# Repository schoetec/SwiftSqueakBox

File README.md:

# SwiftSqueakBox

Een klein toestel (7cmx7cm) om het geluid van Gierzwaluwen te produceren met als doel zwaluwen naar nest-plaatsen te lokken.

**Waarschijnlijk ben je hier geraakt door de gierzwaluwcontactdag.** 

De Gierzwaluwwerkgroep vlaanderen :
https://www.natuurpunt.be/afdelingen/gierzwaluwenwerkgroep-vlaanderen

Email voor opmerkingen,vragen, bestellingen van printplaatjes of afgewerkte SSB's (enkel versie 3): swiftsqueakbox@gmail.com

**Belangrijk : de hier beschreven schakeling is enkel getest met de MP3 module, DFPlayer van DFRobot (https://www.dfrobot.com/product-1121.html). Wees voorzichtig met bv de MP3-TF-16P, deze ziet er gelijkaardig uit, maar is niet hetzelfde !! (En deze worden soms aangeboden onder de naam van DFPlayer !! ).
De software versie V5.1 werkt ook met MP3-TF-16P (myPlayer_attiny85_v5.1). Onderzoek naar een alternatief zonder deze module is gestart. Meer hierover later.**  

**Voor handleiding en ontwerp beschrijving zie de [project Wiki](https://github.com/schoetec/SwiftSqueakBox/wiki).**
 
**Het project is volledig open source/open hardware en de toegankelijkheid maakt dit een mooi STEM project**

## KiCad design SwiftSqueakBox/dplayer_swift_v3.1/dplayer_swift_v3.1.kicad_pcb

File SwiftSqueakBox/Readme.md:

# Structuur beschrijving

1. Arduino_Swift : bevat de software voor ATTiny84 en ATTiny85/45
2. dplayer_swift_v3.1 : Bevat de kicad 6.0 schema en PCB ontwerp files
3. KiCad_Arduino_Nano_DFPlayer_footprints-master : Bevat het ontwerp voor de DFPlayer kicad footprint.

# Bron verwijzingen:

## Arduino libraries voor dfplayer 
### DFPlayer - A Mini MP3 Player For Arduino

> DFPlayer - A Mini MP3 Player For Arduino
> https://www.dfrobot.com/index.php?route=product/product&product_id=1121
>
> This example shows the all the function of library for DFPlayer.
>
> Created 2016-12-07
> By [Angelo qiao](Angelo.qiao@dfrobot.com)
> 
> GNU Lesser General Public License.
> See <http://www.gnu.org/licenses/> for details.
> All above must be included in any redistribution
> 
> Notice and Trouble shooting
> 
> 1.Connection and Diagram can be found here
> https://www.dfrobot.com/wiki/index.php/DFPlayer_Mini_SKU:DFR0299#Connection_Diagram
> 2.This code is tested on Arduino Uno, Leonardo, Mega boards.

## Kicad footprint design. (deze heb je nodig voor de kicad PCB, dus eerst deze footprint opladen in de kicad footprint library)
### KiCad_Arduino_Nano_DFPlayer_footprints
> Footprints for Arduino Nano and DFPlayer MP3 player because I had to make them. 
>
> (I actually use a 32 pin socket to hold the nano to the board. eBay: 32 pin dip IC socket. 2x16.)
>
> There are already components out there for both, but I couldnt find a footprint.
>
> How
> * Add to your library directory.
> * Example: C:\Program Files\KiCad\share\kicad\library
> * Add library to Cvpcb app. Preferences->footprint libraries-> append with wizard

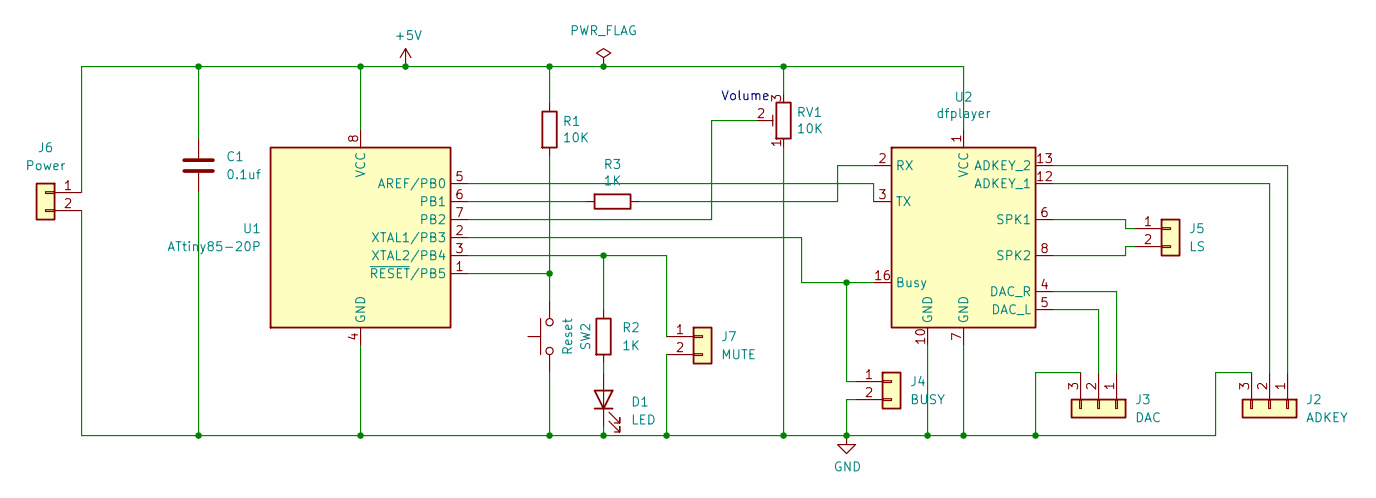
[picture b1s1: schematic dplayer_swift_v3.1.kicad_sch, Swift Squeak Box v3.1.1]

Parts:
C1: 0.1uf; C_Rect_L4.6mm_W2.0mm_P2.50mm_MKS02_FKP02
D1: LED; LED_D3.0mm
J2: ADKEY; JST_PH_B3B-PH-K_1x03_P2.00mm_Vertical
J3: DAC; JST_PH_B3B-PH-K_1x03_P2.00mm_Vertical
J4: BUSY; JST_PH_B2B-PH-K_1x02_P2.00mm_Vertical
J5: LS; JST_PH_B2B-PH-K_1x02_P2.00mm_Vertical
J6: Power; JST_PH_B2B-PH-K_1x02_P2.00mm_Vertical
J7: MUTE; JST_PH_B2B-PH-K_1x02_P2.00mm_Vertical
R1: 10K; R_Axial_DIN0207_L6.3mm_D2.5mm_P7.62mm_Horizontal
R2, R3: 1K; R_Axial_DIN0207_L6.3mm_D2.5mm_P7.62mm_Horizontal
RV1: 10K; Potentiometer_Piher_PT-10-V10_Vertical
SW2: Reset; SW_PUSH_6mm_H4.3mm
U1: ATtiny85-20P; DIP-8_W7.62mm
U2: dfplayer; DFPlayer

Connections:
+5V: C1.1, J6.1, R1.1, RV1.3, U1.8 (VCC), U2.1 (VCC)
GND: C1.2, D1.1 (K), J2.3, J3.3, J4.2, J6.2, J7.2, RV1.1, SW2.1, U1.4 (GND), U2.7 (GND), U2.10 (GND)
unnamed: D1.2 (A), R2.2
unnamed: J2.1, U2.13 (ADKEY_2)
unnamed: J2.2, U2.12 (ADKEY_1)
unnamed: J3.1, U2.4 (DAC_R)
unnamed: J3.2, U2.5 (DAC_L)
unnamed: J4.1, U1.2 (XTAL1/PB3), U2.16 (Busy)
unnamed: J5.1, U2.6 (SPK1)
unnamed: J5.2, U2.8 (SPK2)
unnamed: R1.2, SW2.2, U1.1 (~RESET/PB5)
unnamed: J7.1, R2.1, U1.3 (XTAL2/PB4)
unnamed: R3.1, U2.2 (RX)
unnamed: R3.2, U1.6 (PB1)
unnamed: RV1.2, U1.7 (PB2)
unnamed: U1.5 (AREF/PB0), U2.3 (TX)

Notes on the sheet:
Volume

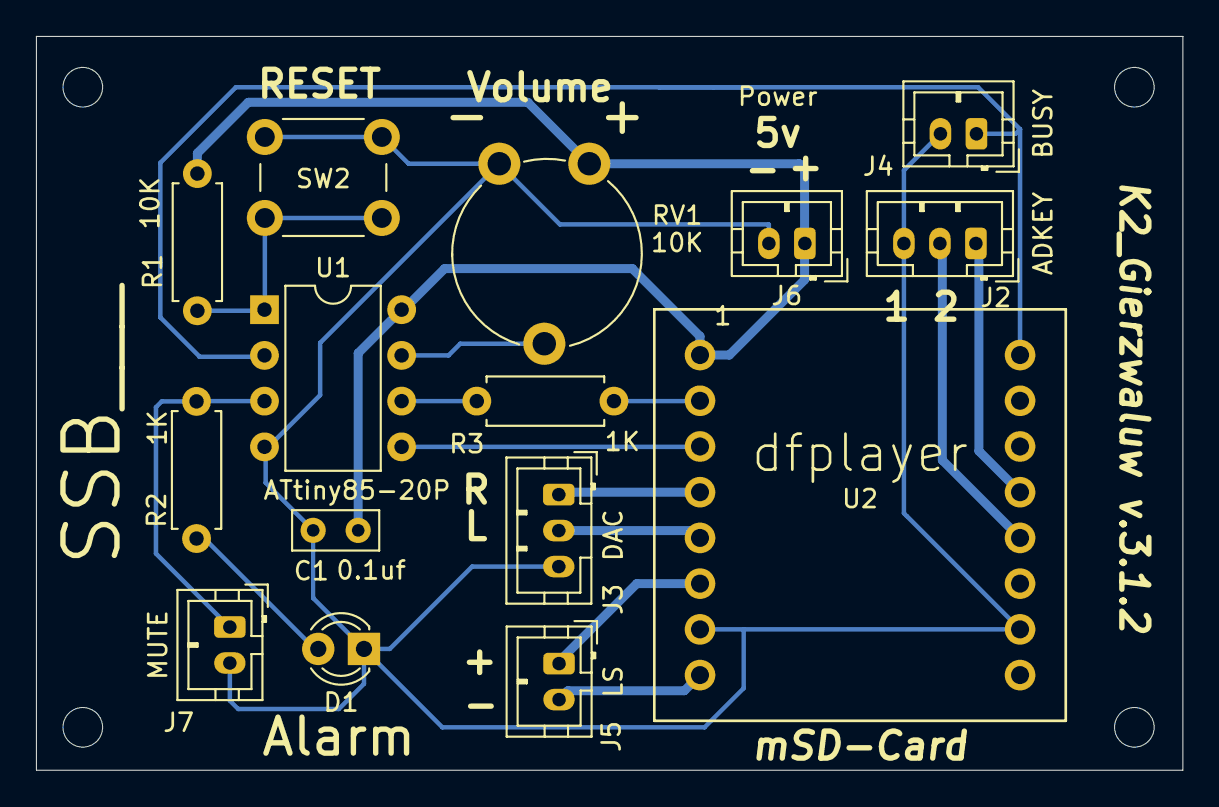
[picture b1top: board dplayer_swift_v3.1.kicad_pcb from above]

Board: 2 copper layers, 63.7 x 40.8 mm, 15 parts (0 on the bottom side), 16 nets.

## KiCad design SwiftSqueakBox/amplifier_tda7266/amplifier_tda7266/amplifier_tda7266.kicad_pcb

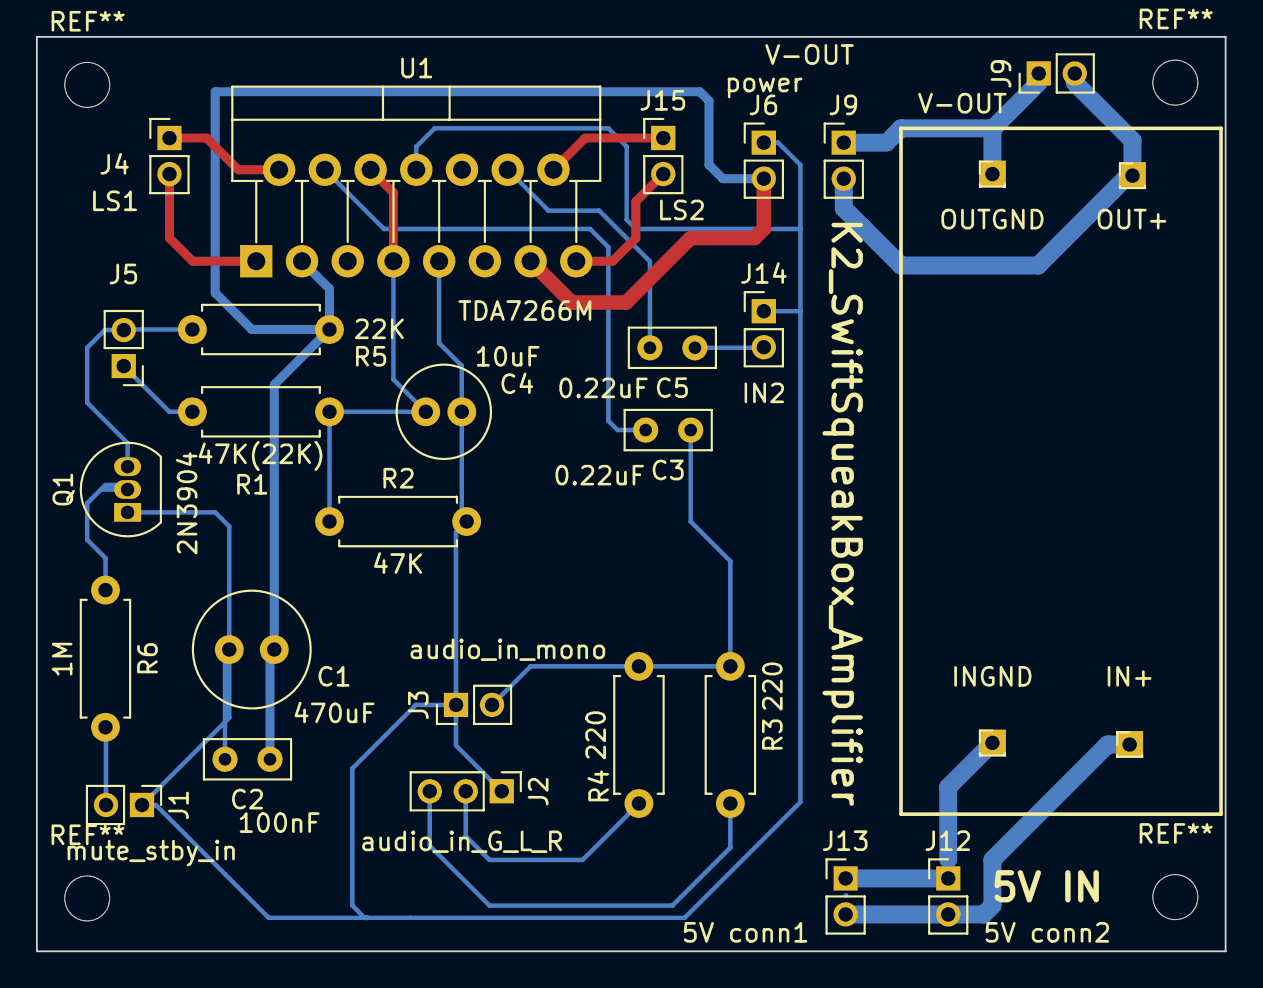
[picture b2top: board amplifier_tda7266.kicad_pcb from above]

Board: 2 copper layers, 66.0 x 50.8 mm, 29 parts (0 on the bottom side), 18 nets.

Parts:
C1: 470uF; C_Radial_D6.3mm_H11.0mm_P2.50mm
C2: 100nF; C_Rect_L4.6mm_W2.0mm_P2.50mm_MKS02_FKP02
C3, C5: 0.22uF; C_Rect_L4.6mm_W2.0mm_P2.50mm_MKS02_FKP02
C4: 10uF; C_Radial_D5.0mm_H11.0mm_P2.00mm
IN+: PinHeader_1x01_P1.00mm_Vertical
INGND: PinHeader_1x01_P1.00mm_Vertical
J1: mute_stby_in; PinHeader_1x02_P2.00mm_Vertical
J2: audio_in_G_L_R; PinHeader_1x03_P2.00mm_Vertical
J3: audio_in_mono; PinHeader_1x02_P2.00mm_Vertical
J4: LS1; PinHeader_1x02_P2.00mm_Vertical
J5: Conn_01x02; PinHeader_1x02_P2.00mm_Vertical
J6: power; PinHeader_1x02_P2.00mm_Vertical
J9, J9#2: V-OUT; PinHeader_1x02_P2.00mm_Vertical
J12: 5V conn2; PinHeader_1x02_P2.00mm_Vertical
J13: 5V conn1; PinHeader_1x02_P2.00mm_Vertical
J14: IN2; PinHeader_1x02_P2.00mm_Vertical
J15: LS2; PinHeader_1x02_P2.00mm_Vertical
OUT+: PinHeader_1x01_P1.00mm_Vertical
OUTGND: PinHeader_1x01_P1.00mm_Vertical
Q1: 2N3904; TO-92_Inline
R1: 47K(22K); R_Axial_DIN0207_L6.3mm_D2.5mm_P7.62mm_Horizontal
R2: 47K; R_Axial_DIN0207_L6.3mm_D2.5mm_P7.62mm_Horizontal
R3, R4: 220; R_Axial_DIN0207_L6.3mm_D2.5mm_P7.62mm_Horizontal
R5: 22K; R_Axial_DIN0207_L6.3mm_D2.5mm_P7.62mm_Horizontal
R6: 1M; R_Axial_DIN0207_L6.3mm_D2.5mm_P7.62mm_Horizontal
U1: TDA7266M; TO-220-15_P2.54x2.54mm_StaggerOdd_Lead4.58mm_Vertical

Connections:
GNDPWR: C1.2, C2.2, C4.2, J1.1, J2.1, J3.1, J6.1, J14.1, Q1.1 (E), R2.2, U1.8 (PG), U1.9 (SG)
unnamed: C3.1, J3.2, R3.1, R4.1
unnamed: C3.2, U1.4 (+)
unnamed: C4.1, R1.2, R2.1, U1.6 (MUTE), U1.7 (STBY)
unnamed: J1.2, R6.2
unnamed: J2.2, R4.2
unnamed: J2.3, R3.2
unnamed: J5.1, R1.1
unnamed: J5.2, Q1.3 (C), R5.2
unnamed: J9.2, J9#2.2, OUT+.1
unnamed: J9.1, J9#2.1, OUTGND.1
unnamed: IN+.1, J12.2, J13.2
unnamed: INGND.1, J12.1, J13.1
unnamed: C5.1, J14.2
unnamed: Q1.2 (B), R6.1
unnamed: J4.2, U1.1
unnamed: J4.1, U1.2
VCC: C1.1, C2.1, J6.2, R5.1, U1.3 (V+), U1.13 (V+)

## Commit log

2023-01-18 Add delay during startup with led indicator
    Ensure that the DFPlayer is started correctly
2023-01-20 Used new library for DFPlayer and mp3_tf_16p
    Added new DFPlayer library and forced it to work with MP3_TF_16P DFPlayer.
2023-05-26 update pcb and schematic
2024-02-13 Add amplifier, minor update to dplayer pcb
2024-02-13 Remove backup folder
2024-03-05 Remove bak file
2024-03-05 Made compatible with V3.0 dfplayer (red dfp)
